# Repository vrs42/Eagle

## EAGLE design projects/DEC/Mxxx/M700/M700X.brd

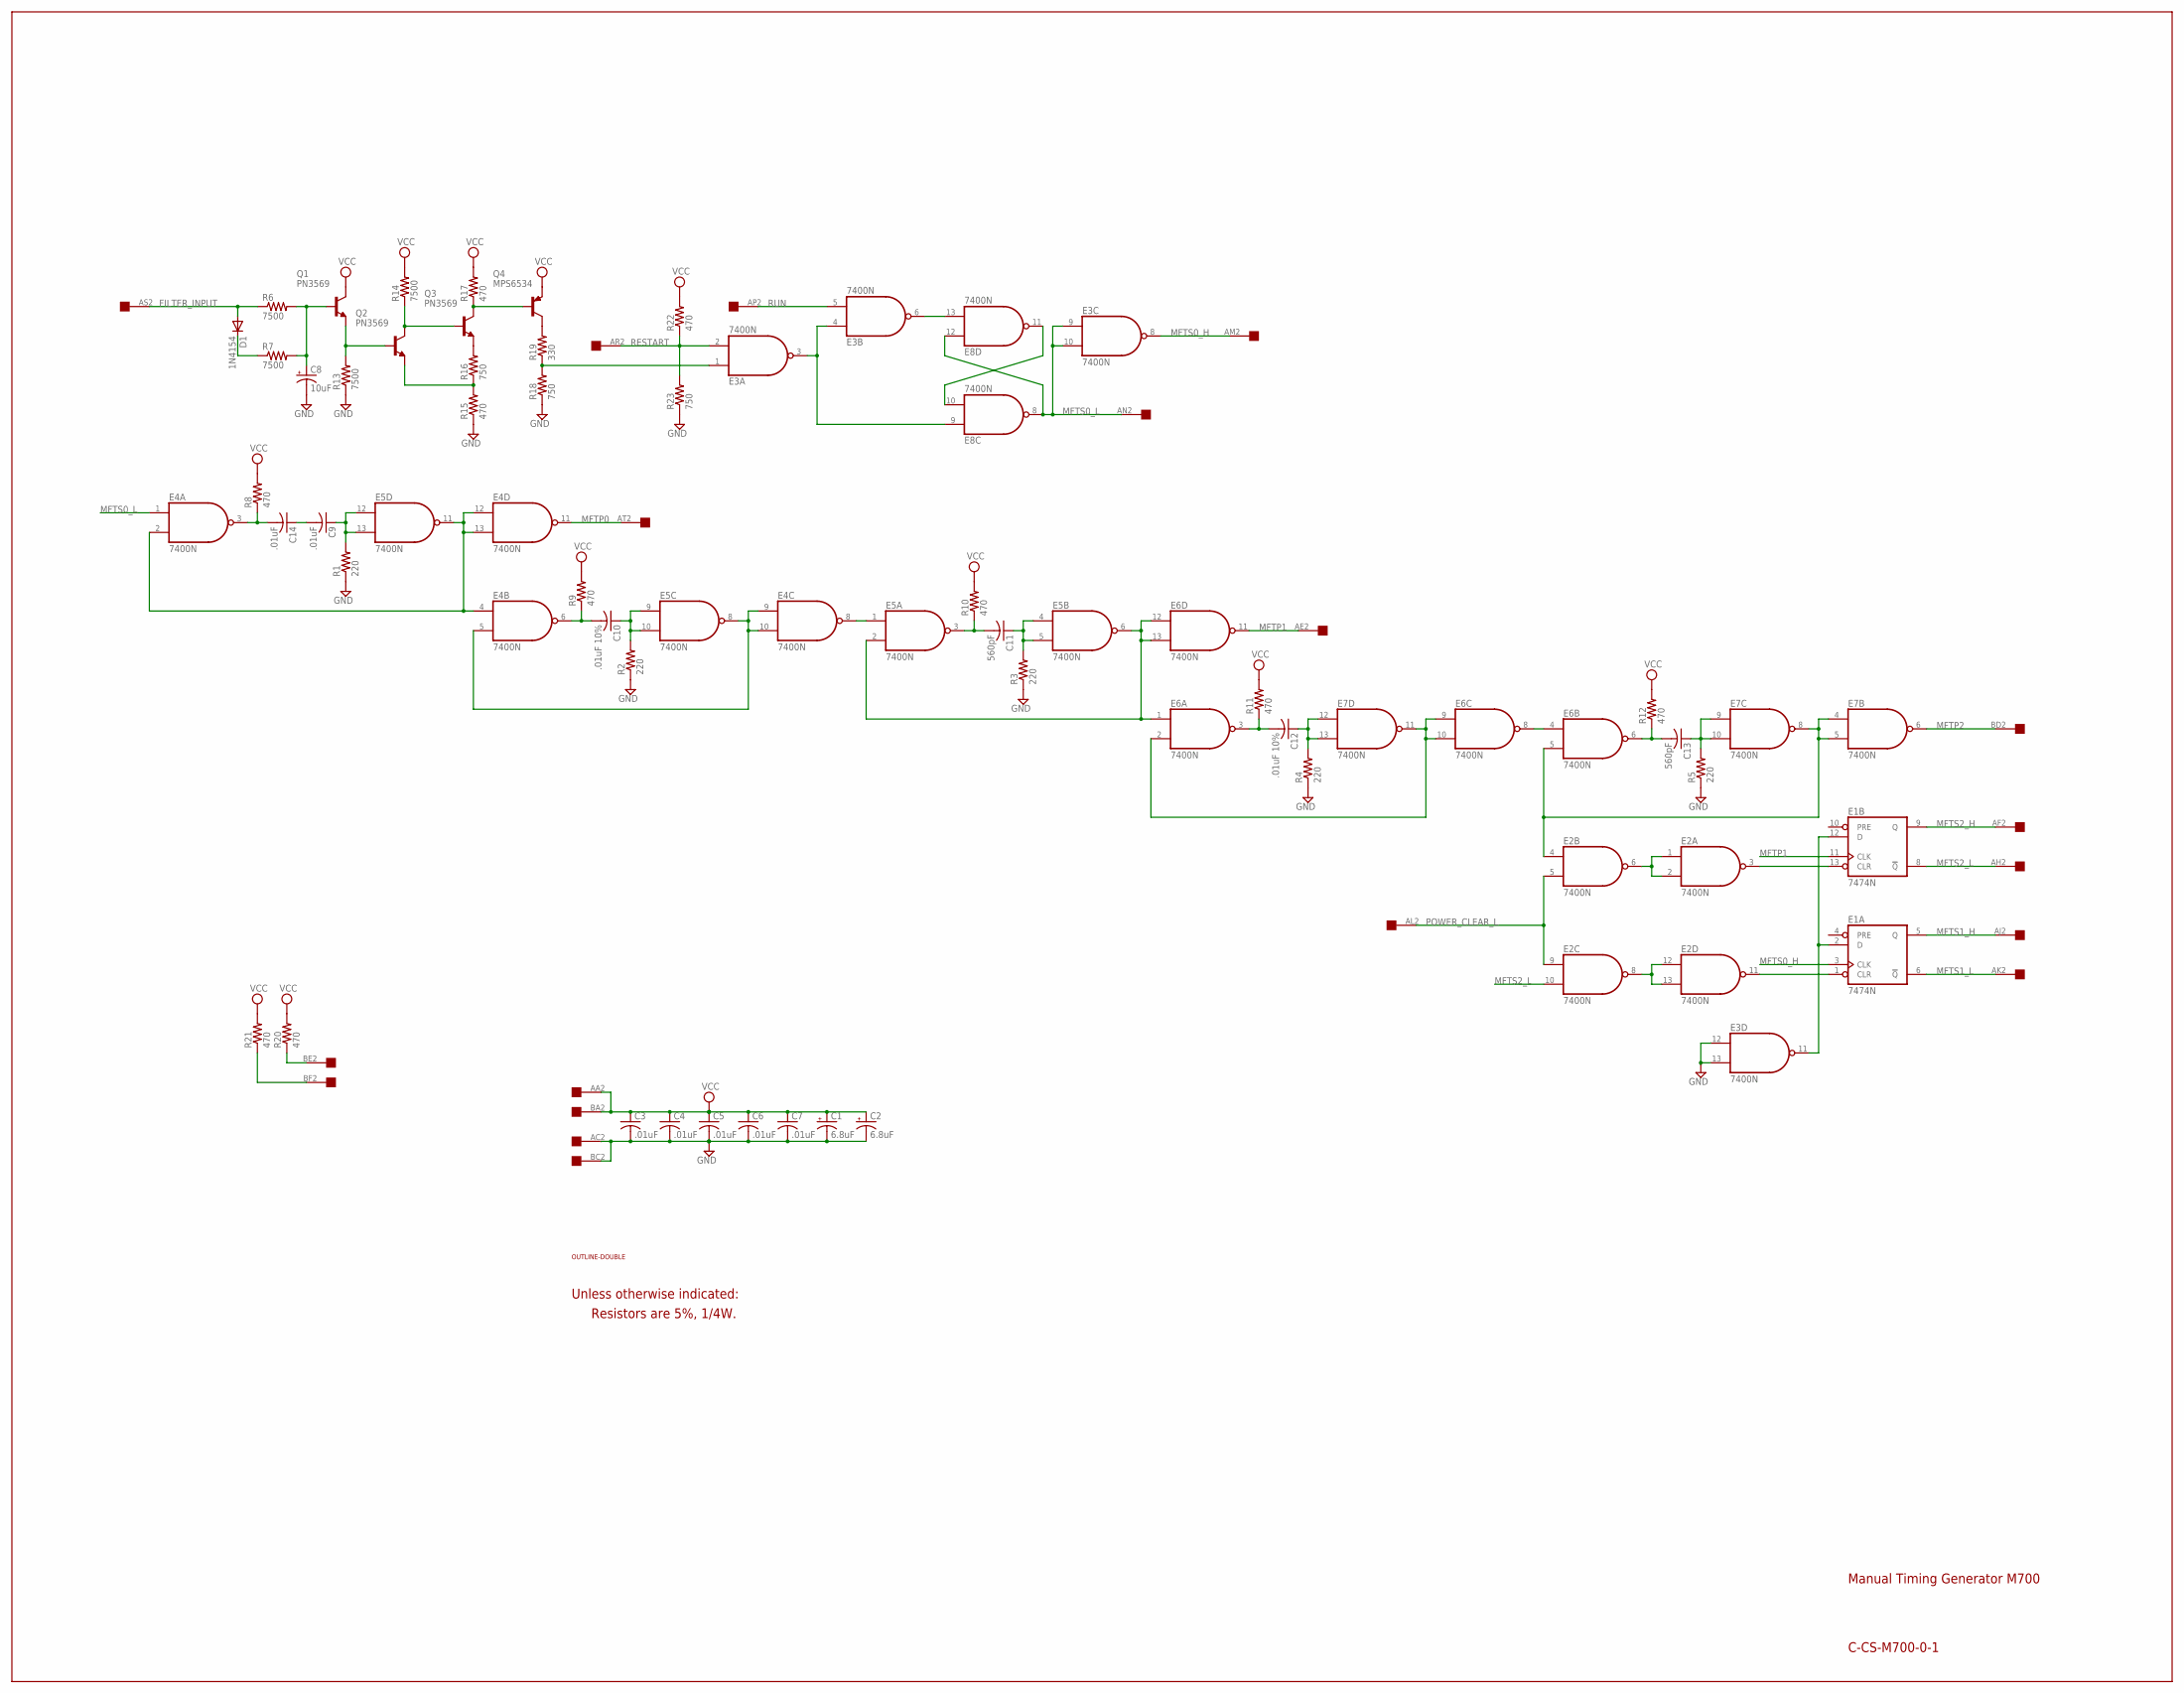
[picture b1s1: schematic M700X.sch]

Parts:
C1, C2: 6.8uF; E12-8
C3, C4, C5, C6, C7: .01uF; C050-025X075
C8: 10uF; E12-8
C9, C14: .01uF; C150-054X183
C10, C12: .01uF 10%; C150-054X183
C11, C13: 560pF; C050-025X075
D1: 1N4154; DO35-10
E1: 7474N; DIL14
E2, E3, E4, E5, E6, E7, E8: 7400N; DIL14
Q1, Q2, Q3: PN3569; TO5
Q4: MPS6534; TO5
R1, R2, R3, R4, R5: 220; 0207/10
R6, R7, R13, R14: 7500; 0207/10
R8, R9, R10, R11, R12, R15, R17, R20, R21, R22: 470; 0207/10
R16, R18, R23: 750; 0207/10
R19: 330; 0207/10
U$1: DOUBLE; EDGE-CON4
U$2: OUTLINE-DOUBLE; DOUBLE

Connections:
FILTER_INPUT: D1.A, R6.1, U$1.AS2
GND: C1.-, C2.-, C3.2, C4.2, C5.2, C6.2, C7.2, C8.-, E1.7 (GND), E2.7 (GND), E3.7 (GND), E3.12 (I0), E3.13 (I1), E4.7 (GND), E5.7 (GND), E6.7 (GND), E7.7 (GND), E8.7 (GND), R1.1, R2.1, R3.1, R4.1, R5.1, R13.1, R15.1, R18.1, R23.1, U$1.AC2, U$1.BC2
MFTP0: E4.11 (O), U$1.AT2
MFTP1: E1.11 (CLK), E6.11 (O), U$1.AE2
MFTP2: E7.6 (O), U$1.BD2
MFTS0_H: E1.3 (CLK), E3.8 (O), U$1.AM2
MFTS0_L: E3.9 (I0), E3.10 (I1), E4.1 (I0), E8.8 (O), E8.12 (I0), U$1.AN2
MFTS1_H: E1.5 (Q), U$1.AJ2
MFTS1_L: E1.6 (!Q), U$1.AK2
MFTS2_H: E1.9 (Q), U$1.AF2
MFTS2_L: E1.8 (!Q), E2.10 (I1), U$1.AH2
unnamed: E1.13 (CLR), E2.3 (O)
unnamed: E2.4 (I0), E6.5 (I1), E7.4 (I0), E7.5 (I1), E7.8 (O)
unnamed: C13.1, E7.9 (I0), E7.10 (I1), R5.2
unnamed: C13.2, E6.6 (O), R12.1
unnamed: E2.1 (I0), E2.2 (I1), E2.6 (O)
unnamed: C8.+, Q1.2 (B), R6.2, R7.2
unnamed: E1.2 (D), E1.12 (D), E3.11 (O)
unnamed: D1.C, R7.1
unnamed: Q2.3 (C), Q3.2 (B), R14.1
unnamed: Q1.1 (E), Q2.2 (B), R13.2
unnamed: R21.1, U$1.BF2
unnamed: R20.1, U$1.BE2
unnamed: Q3.3 (C), Q4.2 (B), R17.1
unnamed: Q3.1 (E), R16.2
unnamed: Q2.1 (E), R15.2, R16.1
unnamed: Q4.3 (C), R19.2
unnamed: E3.1 (I0), R18.2, R19.1
unnamed: E3.3 (O), E3.4 (I0), E8.9 (I0)
unnamed: E8.10 (I1), E8.11 (O)
unnamed: C9.1, E5.12 (I0), E5.13 (I1), R1.2
unnamed: E3.6 (O), E8.13 (I1)
unnamed: C14.2, E4.3 (O), R8.1
unnamed: C9.2, C14.1
unnamed: E4.2 (I1), E4.4 (I0), E4.12 (I0), E4.13 (I1), E5.11 (O)
unnamed: C10.2, E4.6 (O), R9.1
unnamed: C10.1, E5.9 (I0), E5.10 (I1), R2.2
unnamed: E4.5 (I1), E4.9 (I0), E4.10 (I1), E5.8 (O)
unnamed: C11.2, E5.3 (O), R10.1
unnamed: E4.8 (O), E5.1 (I0)
unnamed: C11.1, E5.4 (I0), E5.5 (I1), R3.2
unnamed: E5.2 (I1), E5.6 (O), E6.1 (I0), E6.12 (I0), E6.13 (I1)
unnamed: C12.2, E6.3 (O), R11.1
unnamed: C12.1, E7.12 (I0), E7.13 (I1), R4.2
unnamed: E6.2 (I1), E6.9 (I0), E6.10 (I1), E7.11 (O)
unnamed: E2.8 (O), E2.12 (I0), E2.13 (I1)
unnamed: E6.4 (I0), E6.8 (O)
unnamed: E1.1 (CLR), E2.11 (O)
POWER_CLEAR_L: E2.5 (I1), E2.9 (I0), U$1.AL2
RESTART: E3.2 (I1), R22.1, R23.2, U$1.AR2
RUN: E3.5 (I1), U$1.AP2
VCC: C1.+, C2.+, C3.1, C4.1, C5.1, C6.1, C7.1, E1.14 (VCC), E2.14 (VCC), E3.14 (VCC), E4.14 (VCC), E5.14 (VCC), E6.14 (VCC), E7.14 (VCC), E8.14 (VCC), Q1.3 (C), Q4.1 (E), R8.2, R9.2, R10.2, R11.2, R12.2, R14.2, R17.2, R20.2, R21.2, R22.2, U$1.AA2, U$1.BA2

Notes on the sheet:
Manual Timing Generator M700
C-CS-M700-0-1
Unless otherwise indicated:
Resistors are 5%, 1/4W.

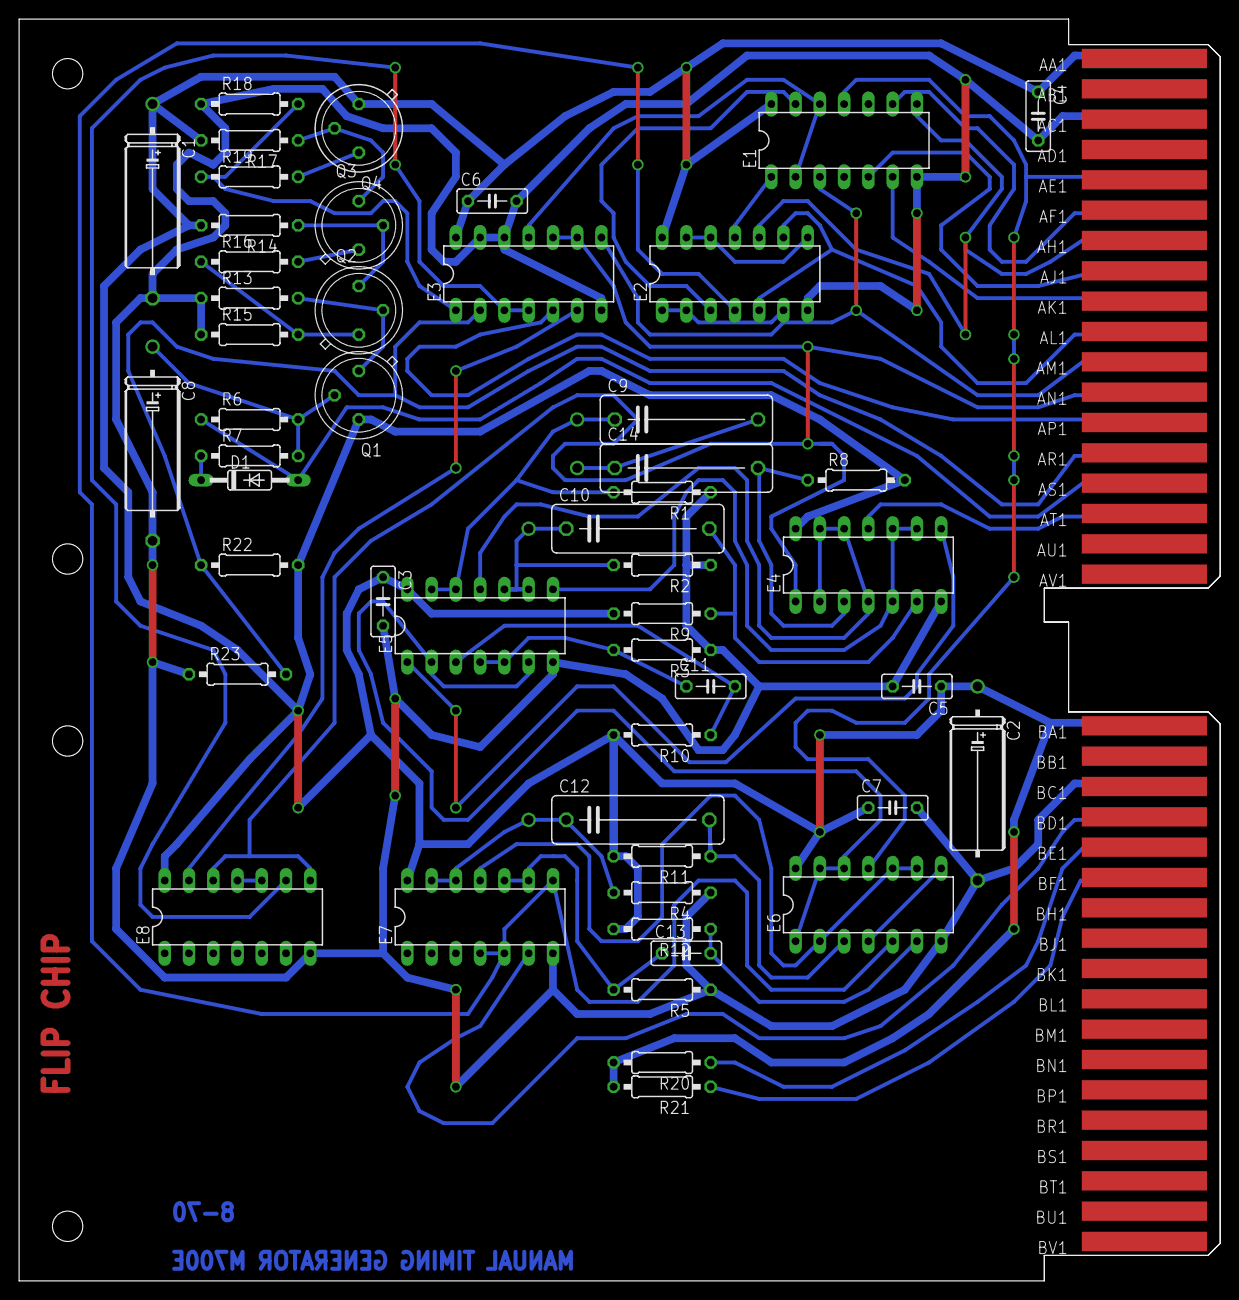
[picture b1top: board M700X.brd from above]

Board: 2 copper layers, 125.7 x 132.1 mm, 53 parts (0 on the bottom side), 52 nets.

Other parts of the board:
U$4: FLIPCHIP

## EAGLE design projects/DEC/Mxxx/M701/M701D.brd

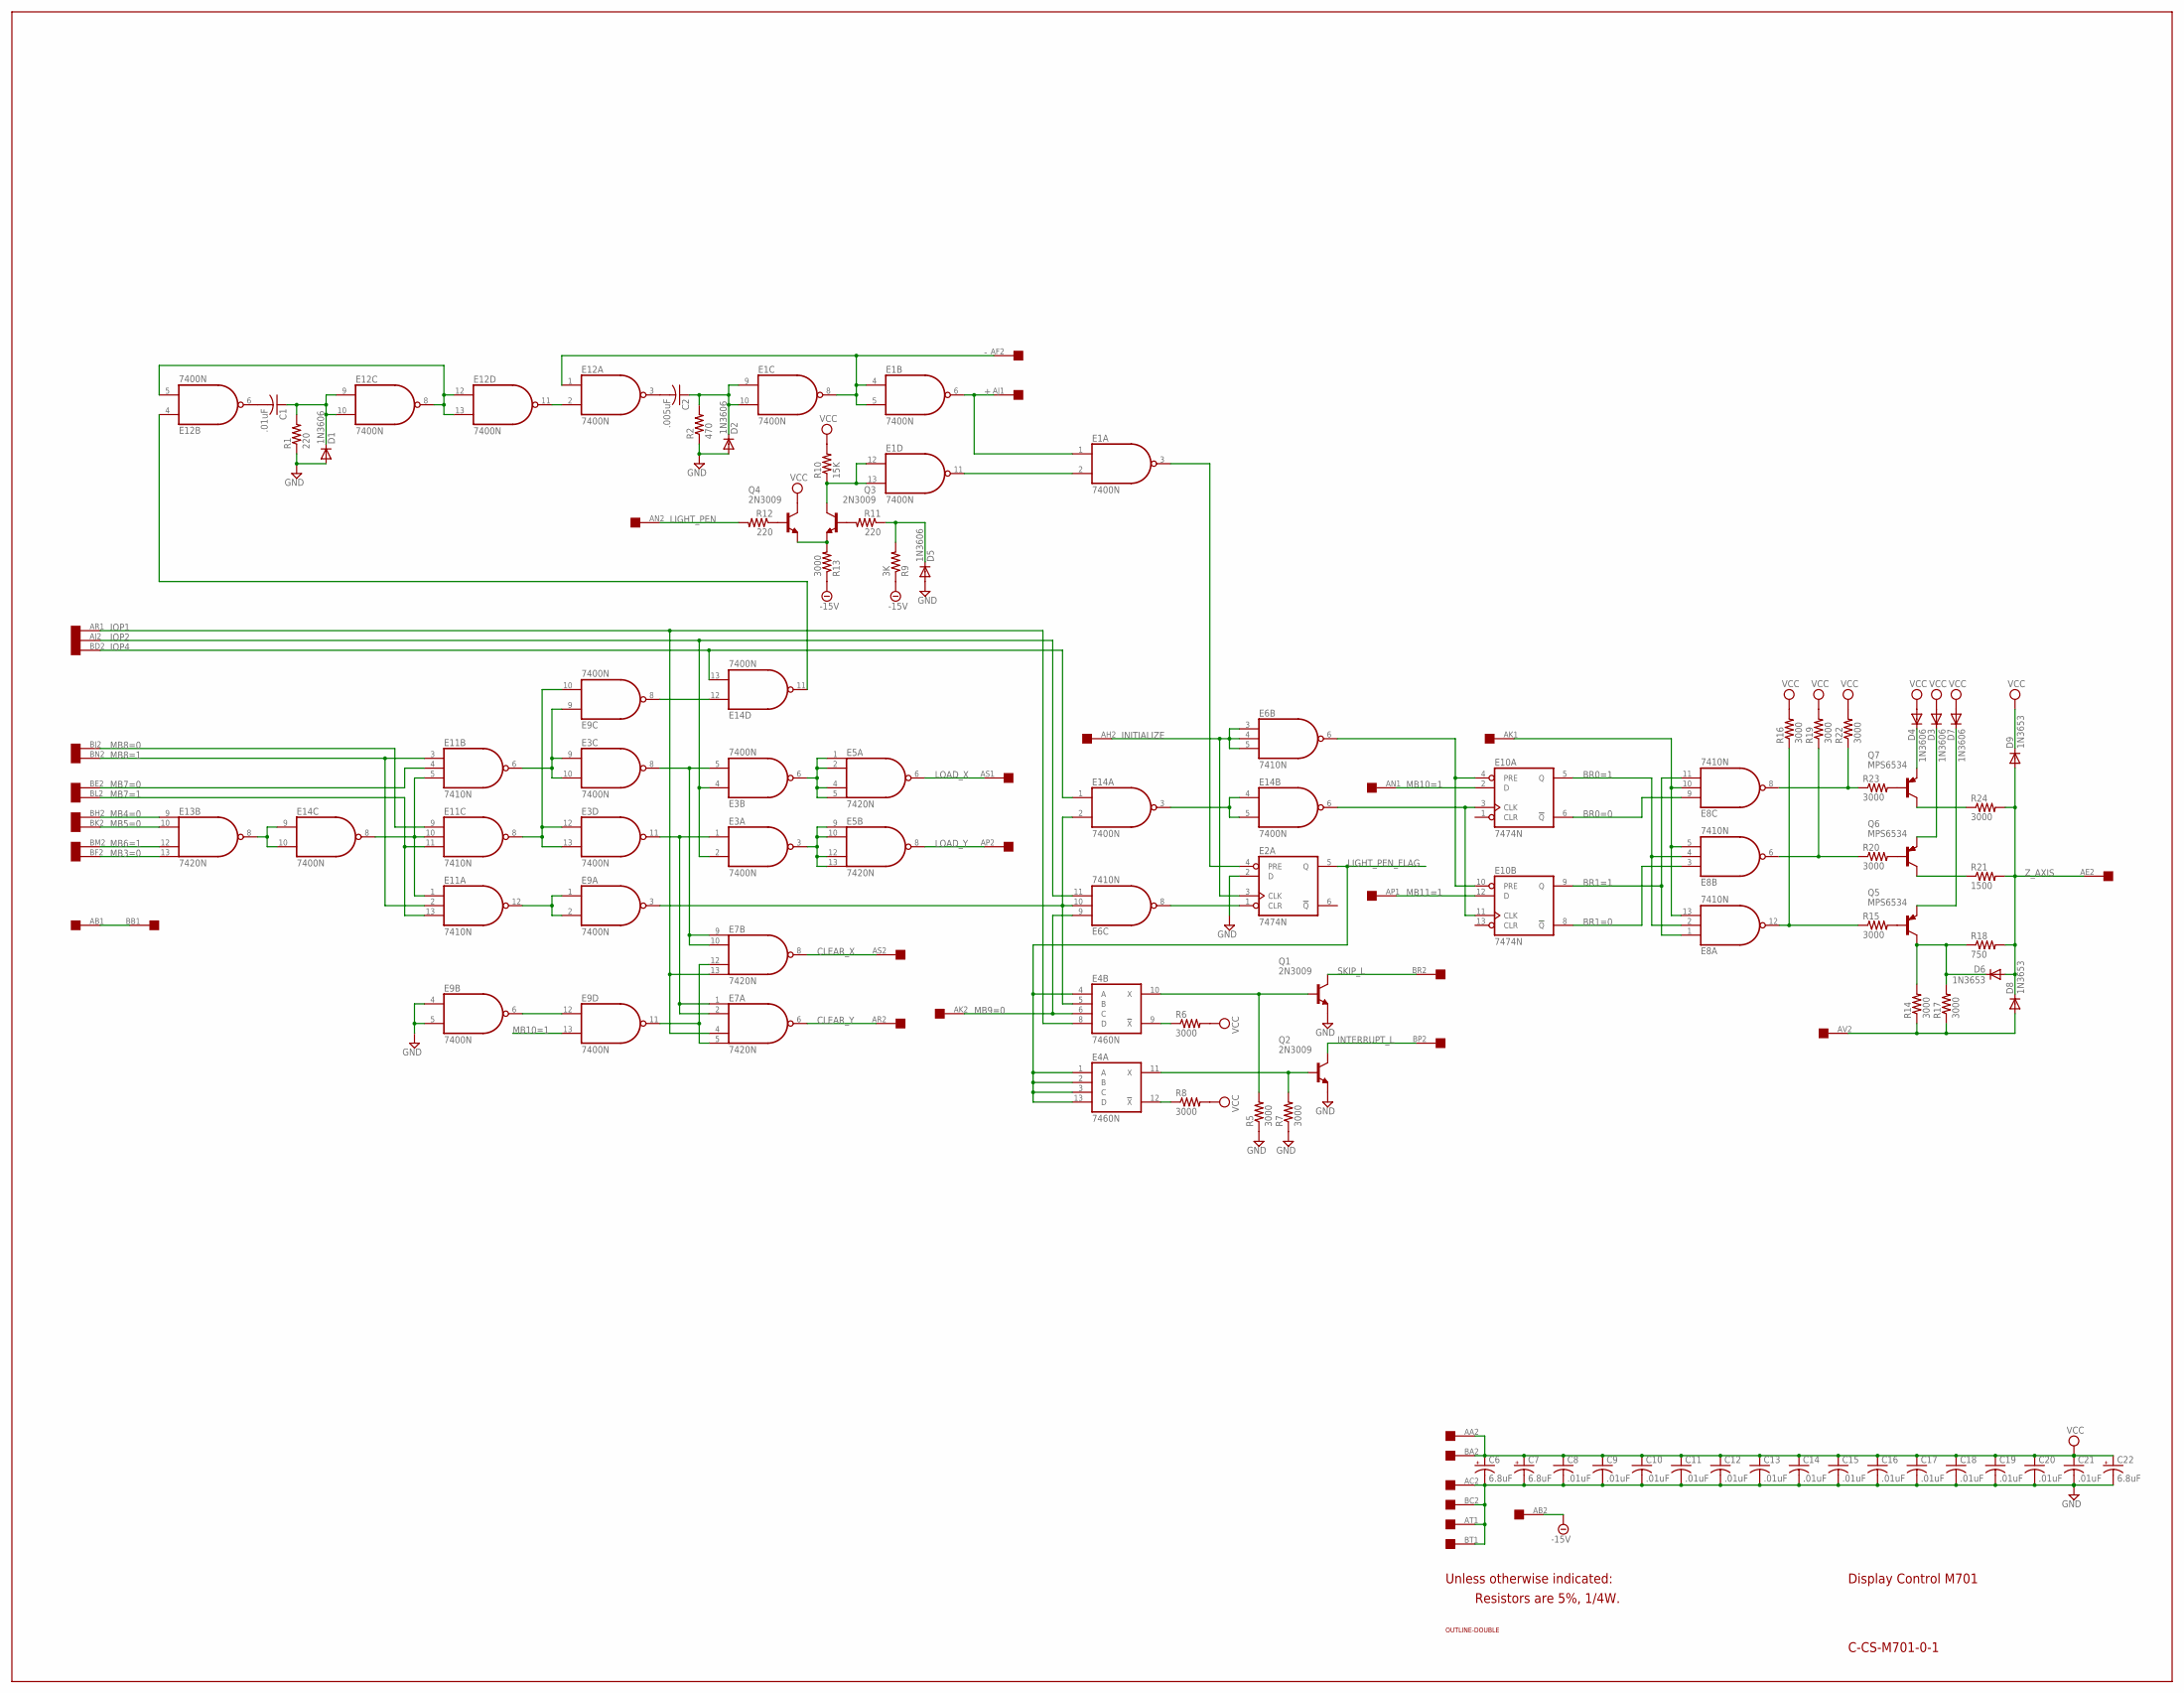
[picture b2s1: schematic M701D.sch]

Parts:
C1, C8, C9, C10, C11, C12, C13, C14, C15, C16, C17, C18, C19, C20, C21: .01uF; C050-025X075
C2: .005uF; C050-025X075
C6, C7, C22: 6.8uF; E12-8
D1, D2, D3, D4, D5, D7: 1N3606; DO35-10
D6, D8, D9: 1N3653; DO35-10
E1, E3, E9, E12, E14: 7400N; DIL14
E2, E10: 7474N; DIL14
E4: 7460N; DIL14
E5, E7, E13: 7420N; DIL14
E6, E8, E11: 7410N; DIL14
Q1, Q2, Q3, Q4: 2N3009; TO5
Q5, Q6, Q7: MPS6534; TO5
R1, R11, R12: 220; 0207/10
R2: 470; 0207/10
R5, R6, R7, R8, R13, R14, R15, R16, R17, R19, R20, R22, R23, R24: 3000; 0207/10
R9: 3K; 0207/10
R10: 15K; 0207/10
R18: 750; 0207/10
R21: 1500; 0207/10
U$1: DOUBLE; EDGE-CON4
U$2: OUTLINE-DOUBLE; DOUBLE

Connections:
+: E1.1 (I0), E1.6 (O), U$1.AJ1
-: E1.4 (I0), E1.5 (I1), E1.8 (O), E12.1 (I0), U$1.AF2
-15V: R9.1, R13.1, U$1.AB2
BR0=0: E8.9 (I0), E10.6 (!Q)
BR0=1: E8.2 (I1), E8.4 (I1), E10.5 (Q)
BR1=0: E8.3 (I0), E10.8 (!Q)
BR1=1: E8.1 (I0), E8.11 (I2), E10.9 (Q)
CLEAR_X: E7.8 (O), U$1.AS2
CLEAR_Y: E7.6 (O), U$1.AR2
GND: C6.-, C7.-, C8.2, C9.2, C10.2, C11.2, C12.2, C13.2, C14.2, C15.2, C16.2, C17.2, C18.2, C19.2, C20.2, C21.2, C22.-, D1.A, D2.A, D5.A, E1.7 (GND), E2.2 (D), E2.7 (GND), E3.7 (GND), E4.7 (GND), E5.7 (GND), E6.7 (GND), E7.7 (GND), E8.7 (GND), E9.4 (I0), E9.5 (I1), E9.7 (GND), E10.7 (GND), E11.7 (GND), E12.7 (GND), E13.7 (GND), E14.7 (GND), Q1.1 (E), Q2.1 (E), R1.1, R2.1, R5.1, R7.1, U$1.AC2, U$1.AT1, U$1.BC2, U$1.BT1
INITIALIZE: E2.3 (CLK), E6.3 (I0), E6.4 (I1), E6.5 (I2), U$1.AH2
INTERRUPT_L: Q2.3 (C), U$1.BP2
IOP1: E4.8 (D), E7.4 (I2), E7.13 (I3), U$1.AR1
IOP2: E3.2 (I1), E3.4 (I0), E6.11 (I2), U$1.AJ2
IOP4: E14.1 (I0), E14.13 (I1), U$1.BD2
LIGHT_PEN: R12.2, U$1.AN2
LIGHT_PEN_FLAG: E2.5 (Q), E4.1 (A), E4.2 (B), E4.3 (C), E4.4 (A), E4.13 (D)
LOAD_X: E5.6 (O), U$1.AS1
LOAD_Y: E5.8 (O), U$1.AP2
MB3=0: E13.13 (I3), U$1.BF2
MB4=0: E13.9 (I0), U$1.BH2
MB5=0: E13.10 (I1), U$1.BK2
MB6=1: E13.12 (I2), U$1.BM2
MB7=0: E11.4 (I1), U$1.BE2
MB7=1: E11.11 (I2), E11.13 (I2), U$1.BL2
MB8=0: E11.9 (I0), U$1.BJ2
MB8=1: E11.2 (I1), E11.3 (I0), U$1.BN2
MB9=0: E4.6 (C), E6.9 (I0), U$1.AK2
MB10=1: E9.13 (I1), E10.2 (D), U$1.AN1
MB11=1: E10.12 (D), U$1.AP1
unnamed: E13.8 (O), E14.9 (I0), E14.10 (I1)
unnamed: E11.1 (I0), E11.5 (I2), E11.10 (I1), E14.8 (O)
unnamed: E9.1 (I0), E9.2 (I1), E11.12 (O)
unnamed: E3.12 (I0), E3.13 (I1), E9.10 (I1), E11.8 (O)
unnamed: E3.9 (I0), E3.10 (I1), E9.9 (I0), E11.6 (O)
unnamed: E3.5 (I1), E3.8 (O), E7.9 (I0), E7.10 (I1)
unnamed: E3.1 (I0), E3.11 (O), E7.1 (I0), E7.2 (I1)
unnamed: E4.12 (!X), R8.1
unnamed: E3.6 (O), E5.1 (I0), E5.2 (I1), E5.4 (I2), E5.5 (I3)
unnamed: E3.3 (O), E5.9 (I0), E5.10 (I1), E5.12 (I2), E5.13 (I3)
unnamed: E9.8 (O), E14.12 (I0)
unnamed: E14.3 (O), E14.4 (I0), E14.5 (I1)
unnamed: E1.3 (O), E2.4 (PRE)
unnamed: E1.12 (I0), E1.13 (I1), Q3.3 (C), R10.1
unnamed: E4.5 (B), E6.10 (I1), E9.3 (O), E14.2 (I1)
unnamed: E2.1 (CLR), E6.8 (O)
unnamed: Q3.1 (E), Q4.1 (E), R13.2
unnamed: E4.9 (!X), R6.1
unnamed: E4.10 (X), Q1.2 (B), R5.2
unnamed: E4.11 (X), Q2.2 (B), R7.2
unnamed: E10.3 (CLK), E10.11 (CLK), E14.6 (O)
unnamed: E6.6 (O), E10.4 (PRE), E10.10 (PRE)
unnamed: Q3.2 (B), R11.2
unnamed: E8.5 (I2), E8.10 (I1), E8.13 (I2), U$1.AK1
unnamed: E1.2 (I1), E1.11 (O)
unnamed: C2.1, D2.C, E1.9 (I0), E1.10 (I1), R2.2
unnamed: C2.2, E12.3 (O)
unnamed: D5.C, R9.2, R11.1
unnamed: Q4.2 (B), R12.1
unnamed: E12.2 (I1), E12.11 (O)
unnamed: E12.5 (I1), E12.8 (O), E12.12 (I0), E12.13 (I1)
unnamed: C1.1, D1.C, E12.9 (I0), E12.10 (I1), R1.2
unnamed: C1.2, E12.6 (O)
unnamed: Q7.2 (B), R23.2
unnamed: Q6.2 (B), R20.2
unnamed: E12.4 (I0), E14.11 (O)
unnamed: Q5.2 (B), R15.2
unnamed: E8.12 (O), R15.1, R16.1
unnamed: E8.6 (O), R19.1, R20.1
unnamed: E8.8 (O), R22.1, R23.1
unnamed: D4.C, Q7.1 (E)
unnamed: D3.C, Q6.1 (E)
unnamed: D7.C, Q5.1 (E)
unnamed: D6.C, Q5.3 (C), R14.2, R17.2, R18.1
unnamed: Q6.3 (C), R21.1
unnamed: Q7.3 (C), R24.1
unnamed: E7.5 (I3), E7.12 (I2), E9.11 (O)
unnamed: D8.A, R14.1, R17.1, U$1.AV2
unnamed: E9.6 (O), E9.12 (I0)
unnamed: U$1.AB1, U$1.BB1
SKIP_L: Q1.3 (C), U$1.BR2
VCC: C6.+, C7.+, C8.1, C9.1, C10.1, C11.1, C12.1, C13.1, C14.1, C15.1, C16.1, C17.1, C18.1, C19.1, C20.1, C21.1, C22.+, D3.A, D4.A, D7.A, D9.C, E1.14 (VCC), E2.14 (VCC), E3.14 (VCC), E4.14 (VCC), E5.14 (VCC), E6.14 (VCC), E7.14 (VCC), E8.14 (VCC), E9.14 (VCC), E10.14 (VCC), E11.14 (VCC), E12.14 (VCC), E13.14 (VCC), E14.14 (VCC), Q4.3 (C), R6.2, R8.2, R10.2, R16.2, R19.2, R22.2, U$1.AA2, U$1.BA2
Z_AXIS: D6.A, D8.C, D9.A, R18.2, R21.2, R24.2, U$1.AE2

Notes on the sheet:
Display Control M701
C-CS-M701-0-1
Unless otherwise indicated:
Resistors are 5%, 1/4W.

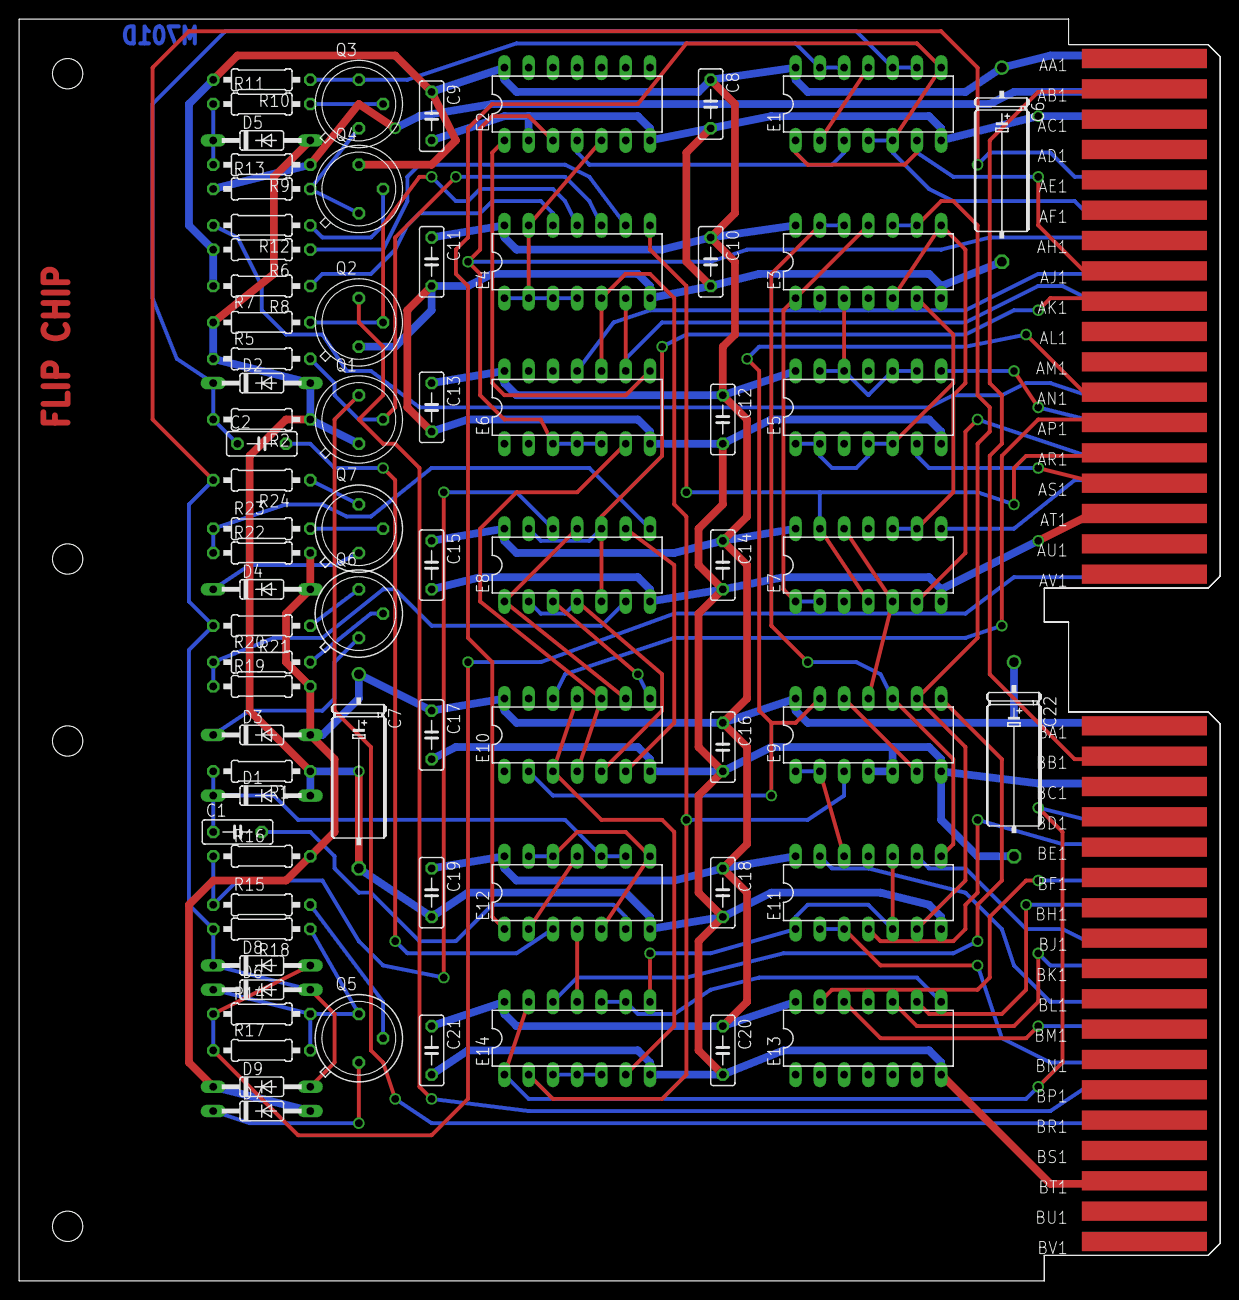
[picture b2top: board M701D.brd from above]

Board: 2 copper layers, 125.7 x 132.1 mm, 74 parts (0 on the bottom side), 83 nets.

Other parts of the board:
U$4: FLIPCHIP
